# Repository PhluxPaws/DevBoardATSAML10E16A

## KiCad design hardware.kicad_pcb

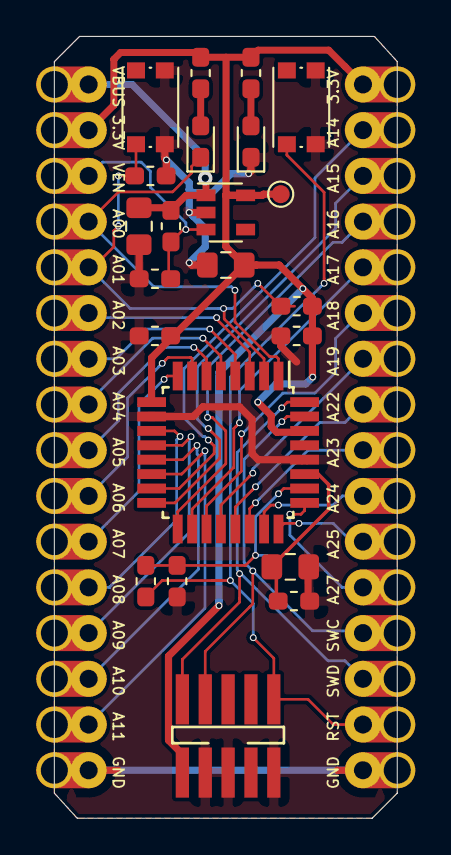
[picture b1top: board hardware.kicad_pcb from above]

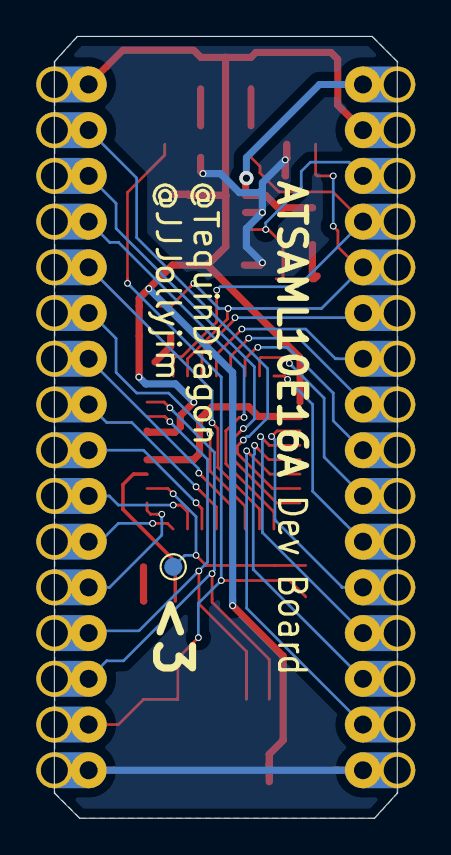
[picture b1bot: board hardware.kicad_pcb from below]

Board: 2 copper layers, 19.0 x 43.4 mm, 25 parts (2 on the bottom side), 34 nets.

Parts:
C1, C2, C7, C8, C10: 100n; C_0603_1608Metric_Pad1.05x0.95mm_HandSolder
C3, C9: 10u; C_0805_2012Metric_Pad1.15x1.40mm_HandSolder
C6: 1u; C_0805_2012Metric_Pad1.15x1.40mm_HandSolder
D1: PA00; LED_0603_1608Metric_Pad1.05x0.95mm_HandSolder
D2: POWER; LED_0603_1608Metric_Pad1.05x0.95mm_HandSolder
J1: SWD; FTSH-105-01-L-DV-K
J2, J3: Conn_01x16_Male; Header_1x16_P2.54mm_Castellated
R1, R2, R4: 330; R_0603_1608Metric_Pad1.05x0.95mm_HandSolder
R3, R6: 10K; R_0603_1608Metric_Pad1.05x0.95mm_HandSolder
R5: NP; R_0603_1608Metric_Pad1.05x0.95mm_HandSolder
SW1: RESET; SW_Push_1P1T_NO_CK_KMR2
SW2: PA01; SW_Push_1P1T_NO_CK_KMR2
TP2: RESET; TestPoint_Pad_D1.0mm
TP4: VOUT; TestPoint_Pad_D1.0mm
U1: ATSAML10E16A-AUT; TQFP-32_7x7mm_P0.8mm
U3: NPC4625HSN33; SOT-23-5

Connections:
/SAML_RESET: C8.2, R1.1, TP2.1, U1.26
/VDDCORE: C6.2, C7.1, U1.27
GND: C1.1, C2.1, C3.1, C6.1, C7.2, C8.1, C9.1, C10.2, D2.1, J1.3, J1.5, J1.9, J2.16, J3.16, R5.1, SW1.2, SW2.2, U1.10, U1.28, U3.2
unnamed: D1.2, R2.1
unnamed: D2.2, R4.1
P3.3: C1.2, C2.2, C3.2, J1.1, J2.2, J3.1, R2.2, R4.2, R6.2, TP4.1, U1.9, U1.30, U3.5
PA00: D1.1, J2.4, U1.1
PA01: C10.1, J2.5, R6.1, SW2.1, U1.2
PA02: J2.6, U1.3
PA03: J2.7, U1.4
PA04: J2.8, U1.5
PA05: J2.9, U1.6
PA06: J2.10, U1.7
PA07: J2.11, U1.8
PA08: J2.12, U1.11
PA09: J2.13, U1.12
PA10: J2.14, U1.13
PA11: J2.15, U1.14
PA14: J3.2, U1.15
PA15: J3.3, U1.16
PA16: J3.4, U1.17
PA17: J3.5, U1.18
PA18: J3.6, U1.19
PA19: J3.7, U1.20
PA22: J3.8, U1.21
PA23: J3.9, U1.22
PA25: J3.11, U1.24
PA27: J3.12, U1.25
PS24: J3.10, U1.23
SWCLK: J1.4, J3.13, U1.31
SWDIO: J1.2, J3.14, U1.32
VBUS: C9.2, J2.1, R3.1, U3.1
VEN: J2.3, R3.2, R5.2, U3.3
~RESET: J1.10, J3.15, R1.2, SW1.1
